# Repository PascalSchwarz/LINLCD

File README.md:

# LINLCD

BOM für ein Display:

|Qty |Value     |              Package   |   Parts   |
|---|---|---|---|
|1  | PIC16(L)F18426| SO-14       | U$3           
|1  | DOGS104-A     | DOGS104-A   | U$1            
|1  | MCP2003       | SO-08       | U$2          
|1  | LD117AS33TR   | SOT223      | IC1       
|1  | BSS123        | SOT23       | Q1              
|1  | 61300611021   | 61300611021 | J2                        
|2  | 690367280676  | 690367280676| J1, J3  
|1  | 10n           | C0603       | C2     
|2  | 100n          | C0603       | C1, C6      
|3  | 1u            | C1206       | C5, C7, C8     
|1  | 10u           | C1206       | C4        
|1  | 100u          | C1206       | C3                                    
|2  | 47            | R0603       | R7, R8                                       
|2  | 470           | R0603       | R2, R9                                      
|3  | 4k7           | R0603       | R3, R5, R6                               
|1  | 10k           | R0603       | R1                                                                
|1  | 220k          | R0603       | R4

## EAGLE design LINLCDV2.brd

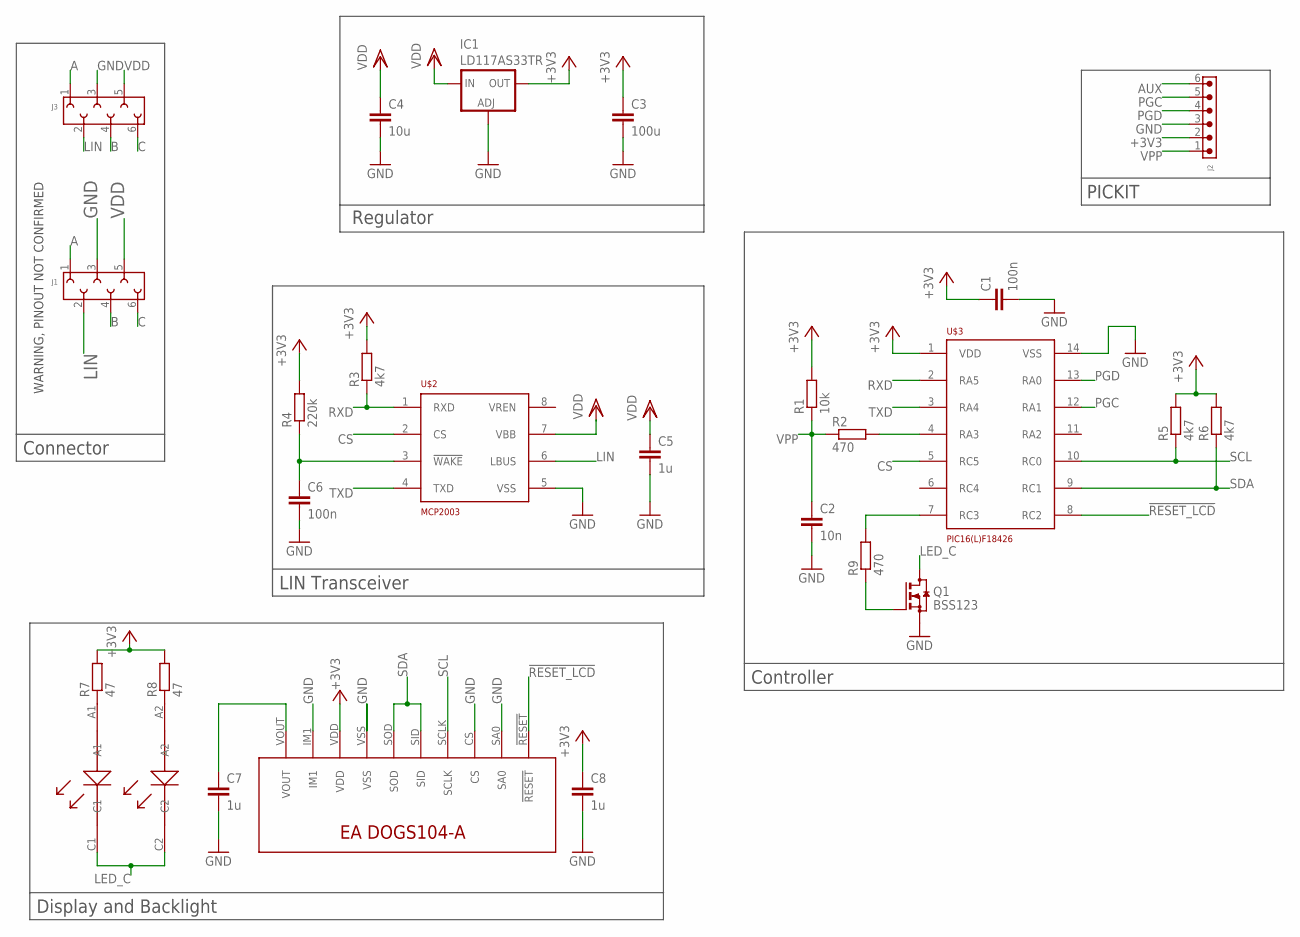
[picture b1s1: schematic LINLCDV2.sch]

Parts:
C1, C6: 100n; C0603
C2: 10n; C0603
C3: 100u; C1206
C4: 10u; C1206
C5, C7, C8: 1u; C1206
IC1: LD117AS33TR; SOT223
J1, J3: 690367280676
J2: 6130XX11021_61300611021; 61300611021
Q1: BSS123; SOT23
R1: 10k; R0603
R2, R9: 470; R0603
R3, R5, R6: 4k7; R0603
R4: 220k; R0603
R7, R8: 47; R0603
U$1: DOGS104-A
U$2: MCP2003; SO-08
U$3: PIC16(L)F18426; SO-14

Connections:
!RESET_LCD: U$1.!RESET, U$3.8 (RC2)
+3V3: C1.1, C3.1, C8.1, IC1.4 (OUT), J2.2, R1.2, R3.2, R4.2, R5.2, R6.2, R7.2, R8.2, U$1.VDD, U$3.1 (VDD)
A: J1.1, J3.1
AUX: J2.6
B: J1.4, J3.4
C: J1.6, J3.6
CS: U$2.2 (CS), U$3.5 (RC5)
GND: C1.2, C2.2, C3.2, C4.2, C5.2, C6.2, C7.2, C8.2, IC1.1 (ADJ), J1.3, J2.3, J3.3, Q1.2 (S), U$1.CS, U$1.IM1, U$1.SA0, U$1.VSS, U$2.5 (VSS), U$3.14 (VSS)
LED_C: Q1.3 (D), U$1.C1, U$1.C2
LIN: J1.2, J3.2, U$2.6 (LBUS)
unnamed: R2.2, U$3.4 (RA3)
unnamed: C6.1, R4.1, U$2.3 (!WAKE)
unnamed: C7.1, U$1.VOUT
unnamed: R7.1, U$1.A1
unnamed: R8.1, U$1.A2
unnamed: R9.2, U$3.7 (RC3)
unnamed: Q1.1 (G), R9.1
PGC: J2.5, U$3.12 (RA1)
PGD: J2.4, U$3.13 (RA0)
RXD: R3.1, U$2.1 (RXD), U$3.2 (RA5)
SCL: R5.1, U$1.SCLK, U$3.10 (RC0)
SDA: R6.1, U$1.SID, U$1.SOD, U$3.9 (RC1)
TXD: U$2.4 (TXD), U$3.3 (RA4)
VDD: C4.1, C5.1, IC1.3 (IN), J1.5, J3.5, U$2.7 (VBB)
VPP: C2.1, J2.1, R1.1, R2.1

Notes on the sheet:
WARNING, PINOUT NOT CONFIRMED
Regulator
LIN Transceiver
Display and Backlight
Connector
Controller
PICKIT

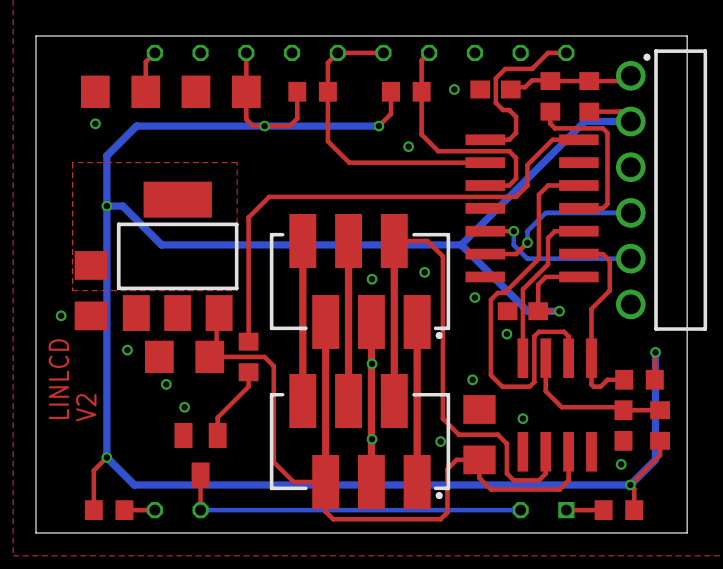
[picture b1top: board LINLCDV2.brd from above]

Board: 2 copper layers, 36.2 x 27.6 mm, 25 parts (1 on the bottom side), 24 nets.

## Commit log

2020-11-08 Add EAGLE PCB files
2020-11-09 Adding BOM

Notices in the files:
parts and their libraries:
Wurth_Connectors_WR-MM: Copyright: Würth Elektronik
